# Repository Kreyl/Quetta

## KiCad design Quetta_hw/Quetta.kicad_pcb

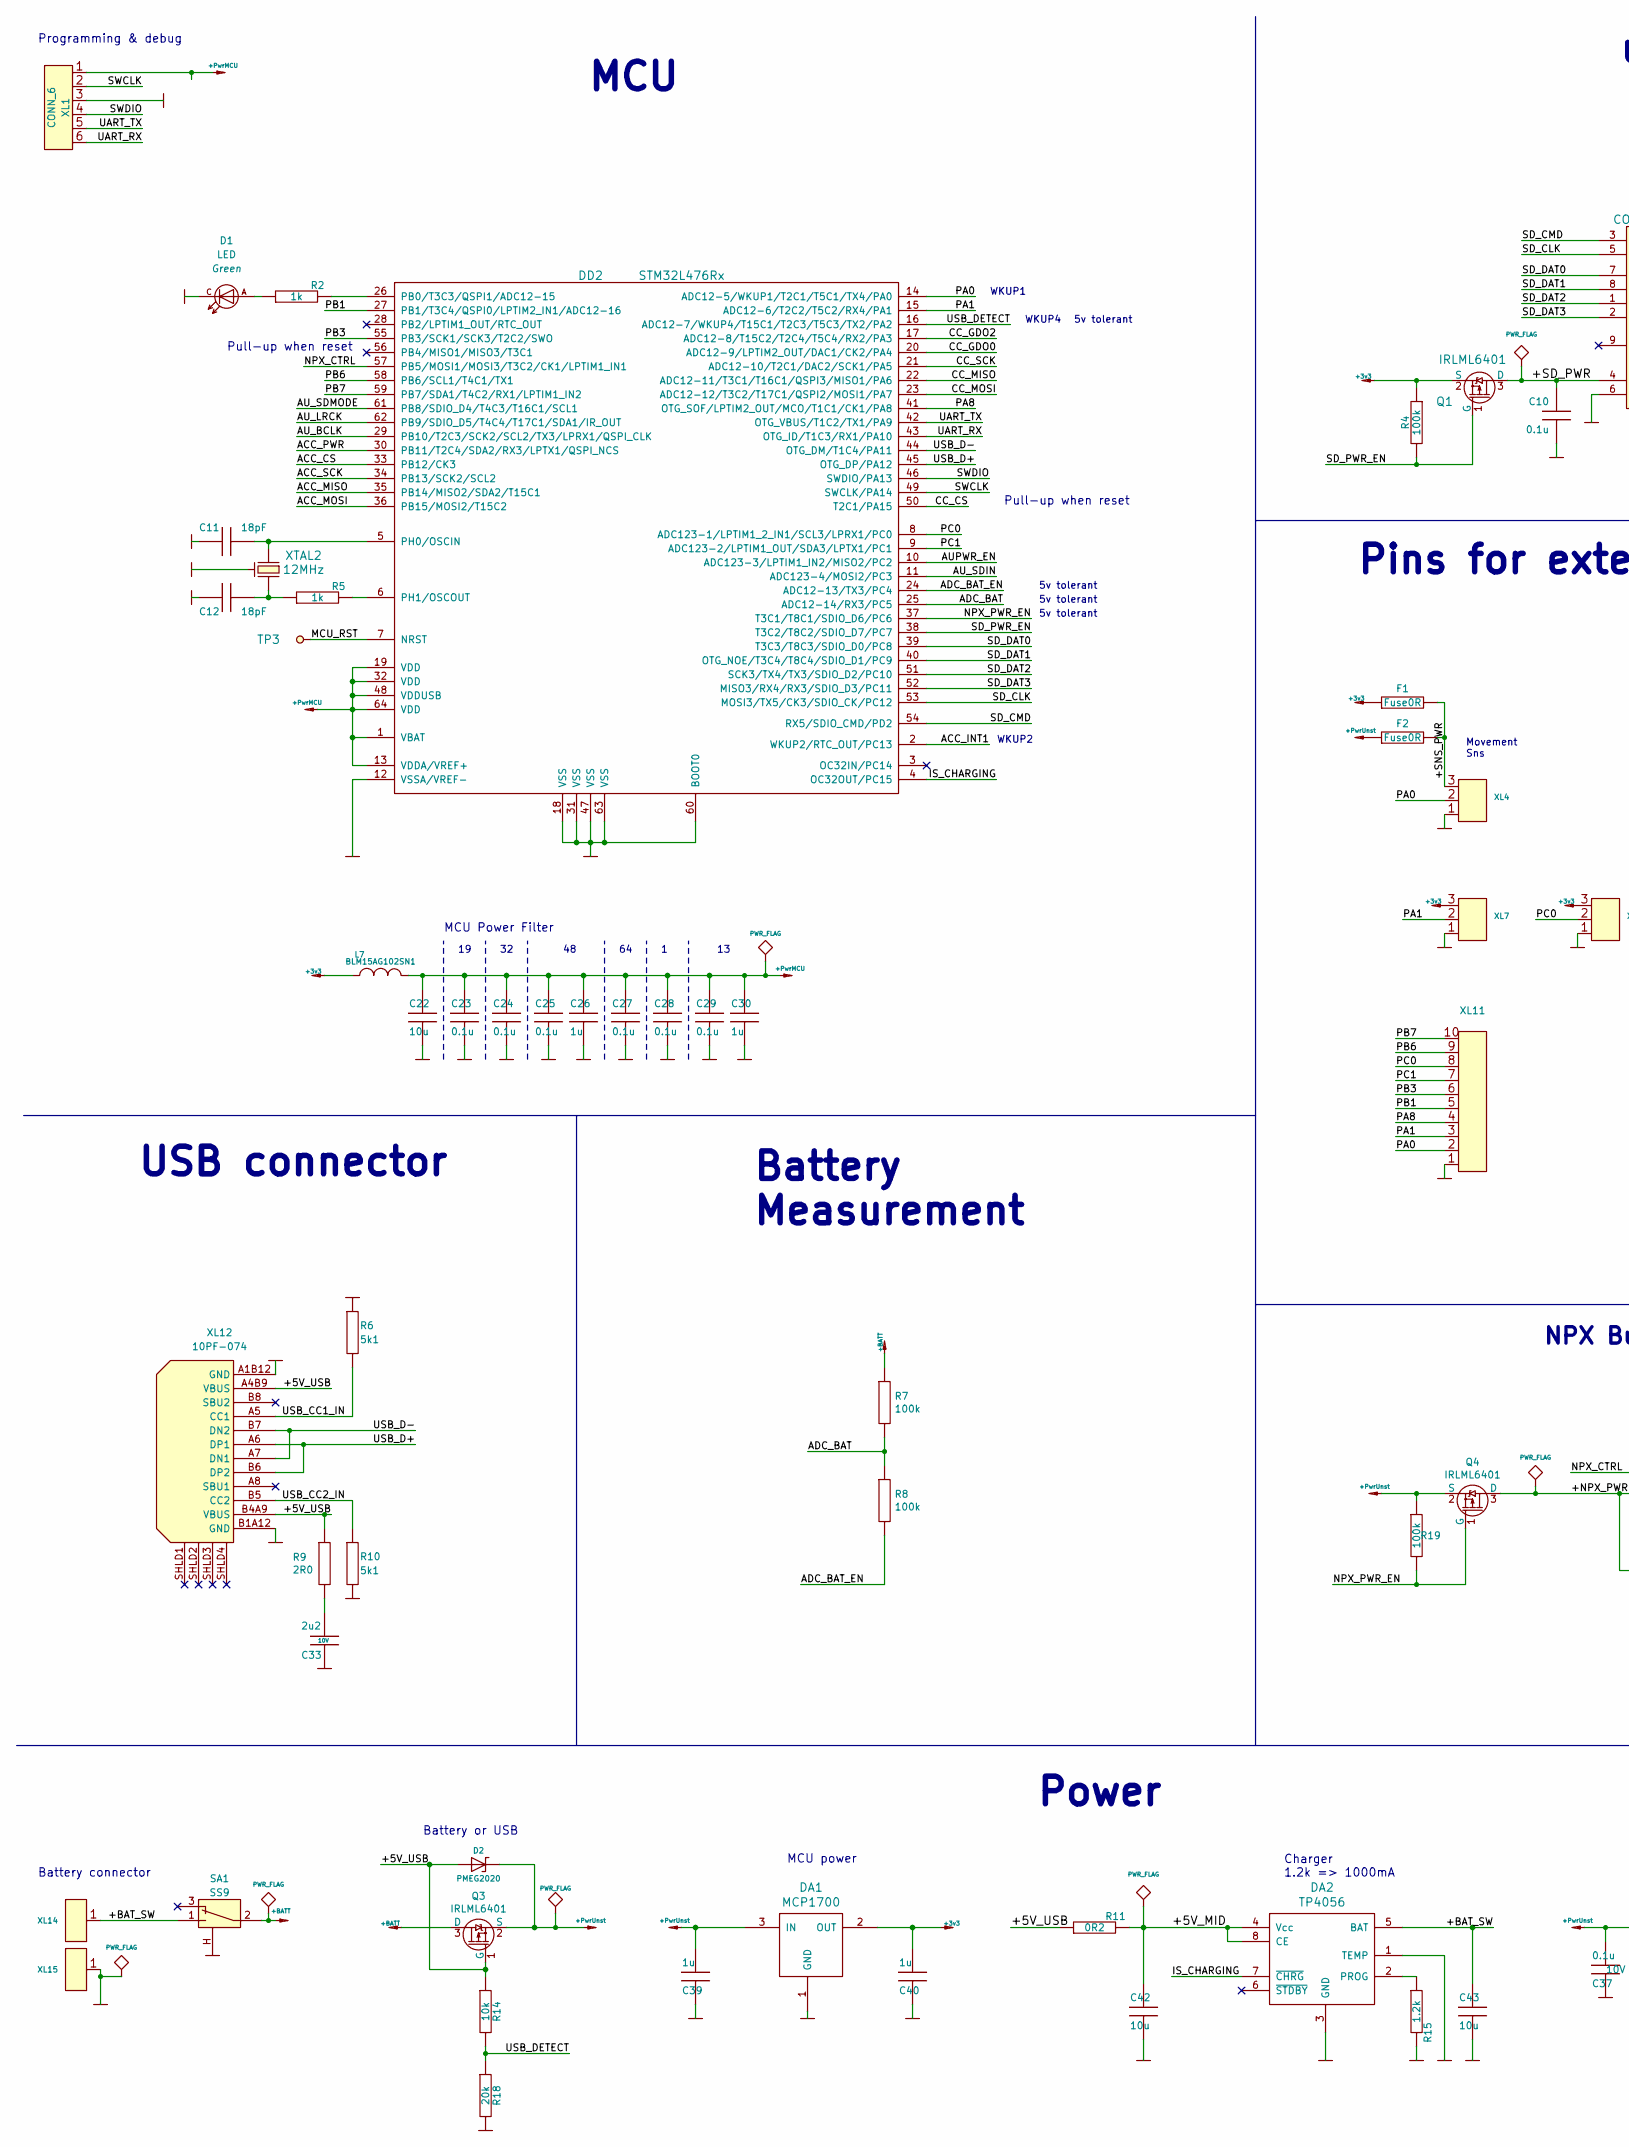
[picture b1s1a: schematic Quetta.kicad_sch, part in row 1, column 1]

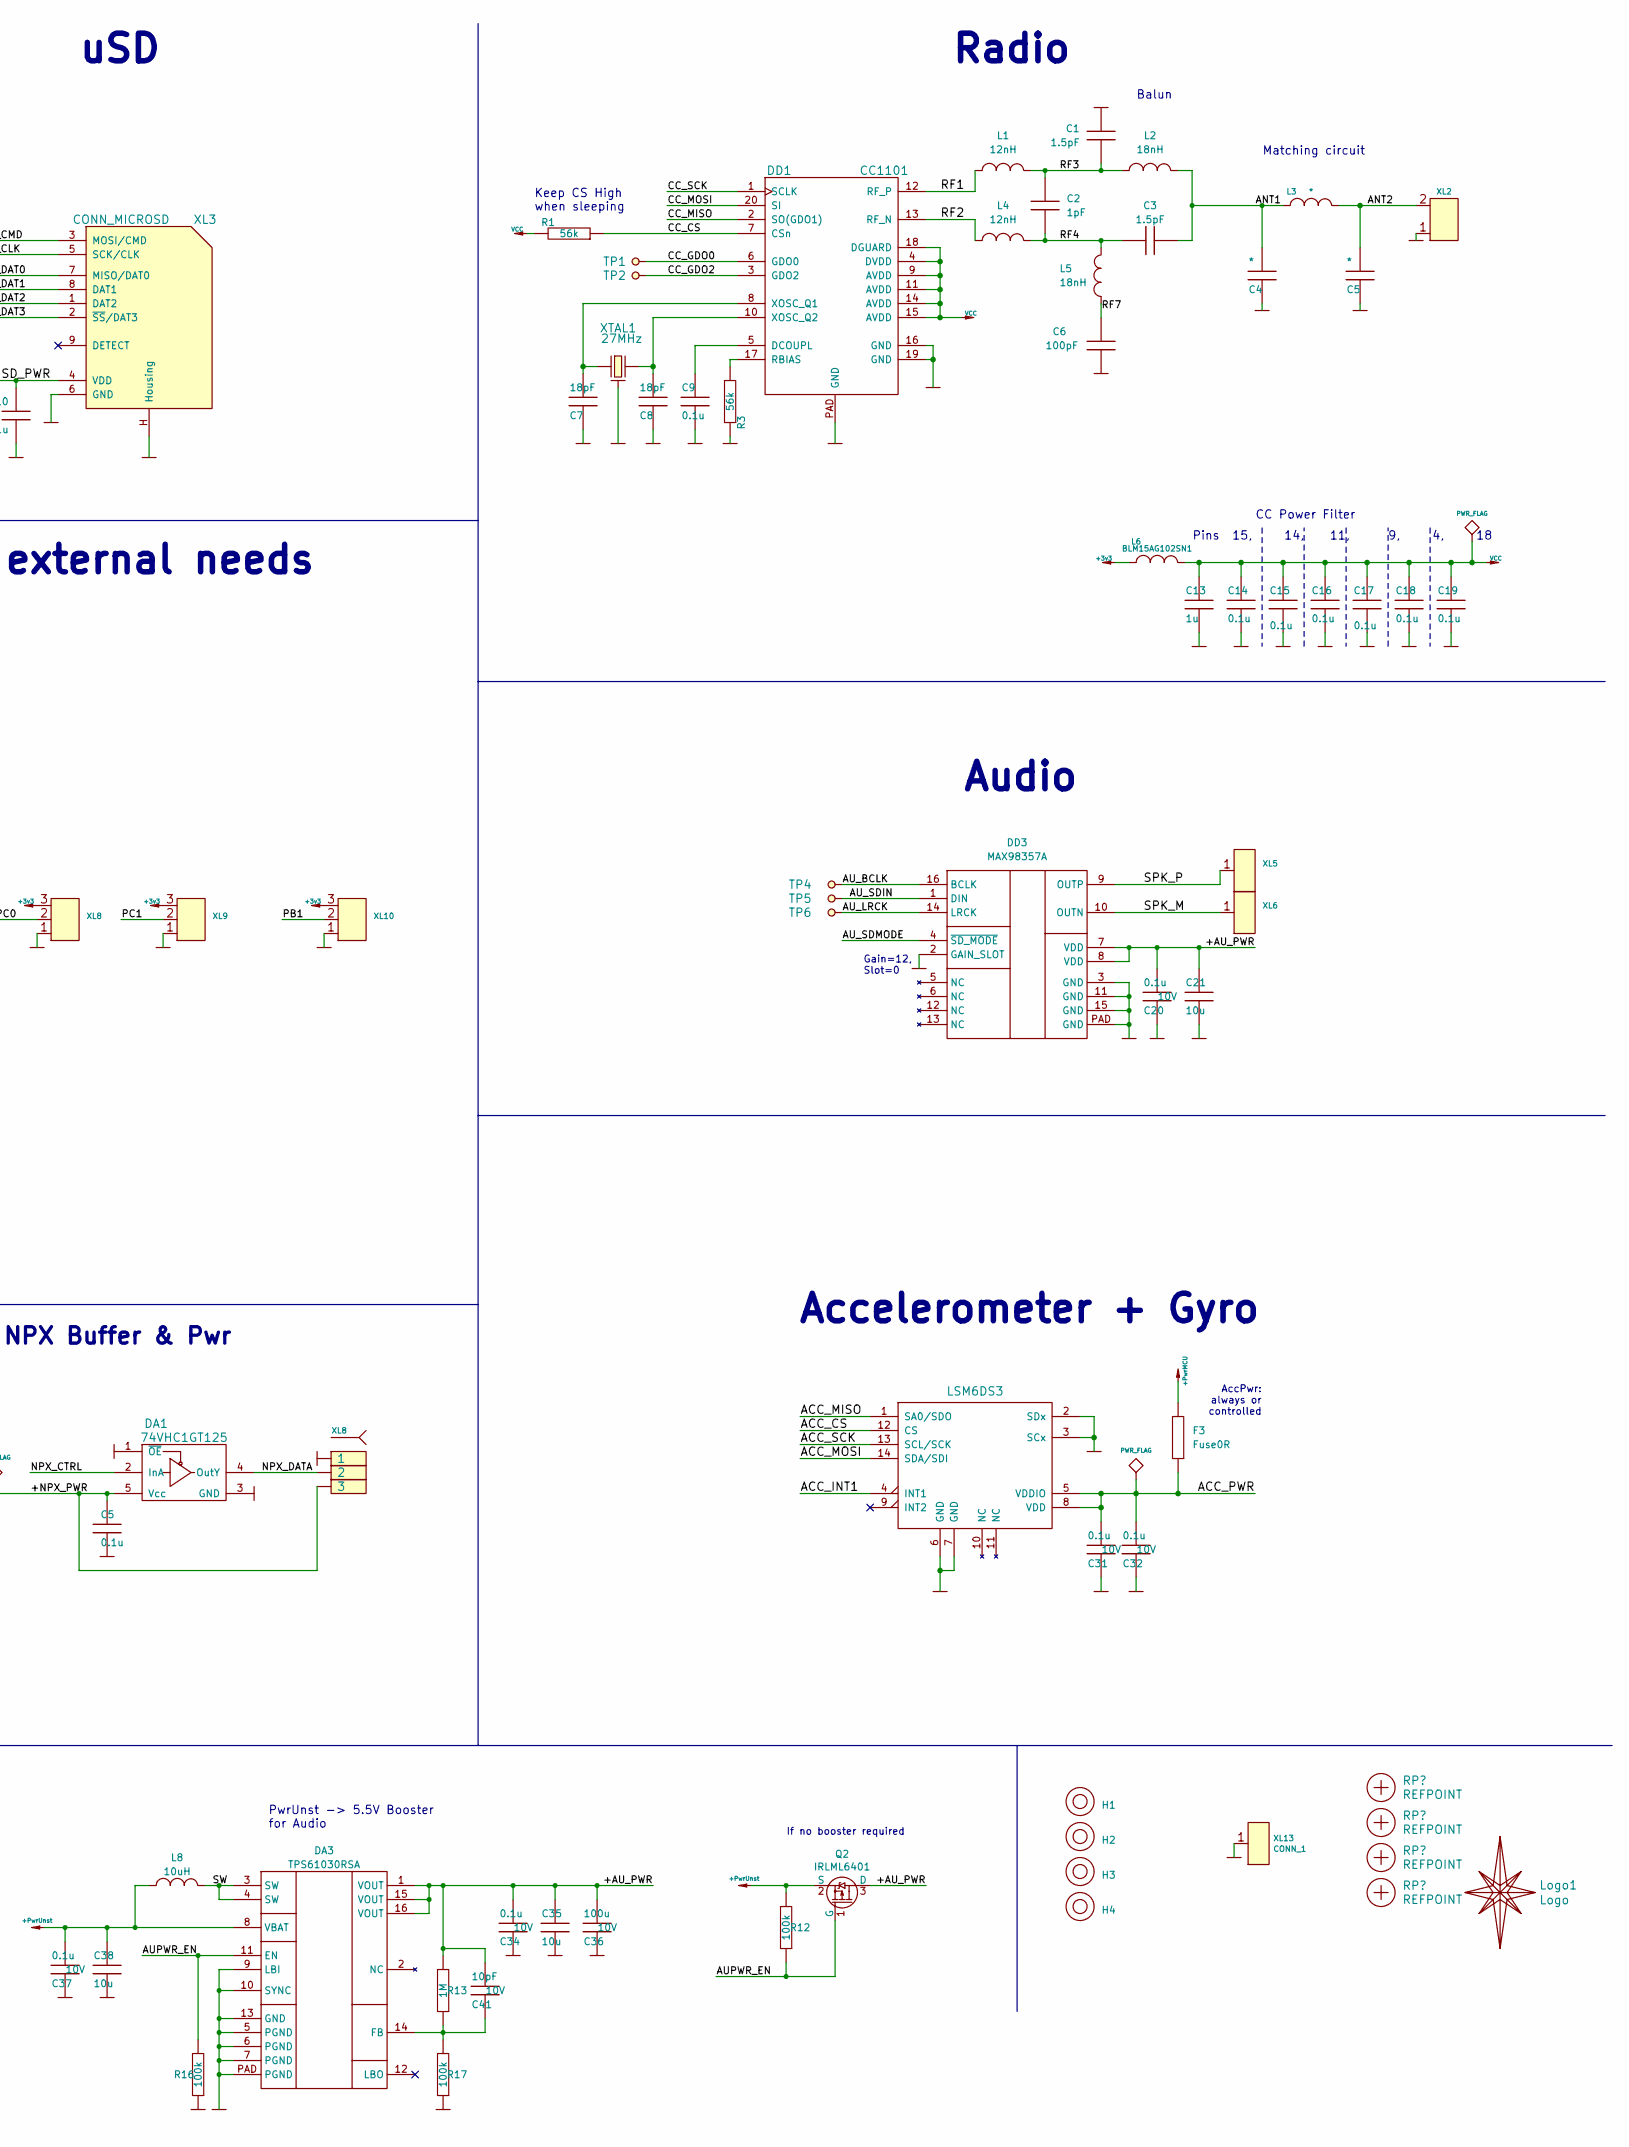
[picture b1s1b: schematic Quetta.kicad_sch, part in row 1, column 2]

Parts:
C1, C3: 1.5pF; CAP_0402; Tolerance 20%; Voltage 10V
C2: 1pF; CAP_0402; Tolerance 20%; Voltage 10V
C4: *; CAP_0402
C5, C20, C31, C32, C34, C37: 0.1u; CAP_0603_Silks; Tolerance 20%; Voltage 10V
C6: 100pF; CAP_0402; Tolerance 20%; Voltage 10V
C7, C8, C11, C12: 18pF; CAP_0603_Silks
C9, C10, C14, C15, C16, C17, C18, C19, C23, C24, C25, C27, C28, C29: 0.1u; CAP_0603_Silks
C13, C26, C30, C39, C40: 1u; CAP_0603_Silks
C21, C22, C35, C38, C42, C43: 10u; CAP_0603_Silks
C33: 2u2; CAP_0603_Silks; Tolerance 20%; Voltage 10V
C36: 100u; CAP_1206; Tolerance 20%; Voltage 10V
C41: 10pF; CAP_0603_Silks; Tolerance 20%; Voltage 10V
D1: LED; LED_0603
D2: PMEG2020; SOD323
DA1: MCP1700; SOT23-3A
DA2: TP4056; SO8_150MIL
DA3: TPS61030RSA; QFN16_0d65_EP2d7
DD1: CC1101; QFN20
DD2: STM32L476Rx; LQFP64
DD3: MAX98357A; QFN-16_EP_3x3_Pitch0.5mm
DD4: LSM6DS3; 14_3x2d5_p0d5
F1, F2, F3: Fuse0R; RES_0603_FUSE
H1, H2, H3, H4: Hole2d2_out4_NoMetal
L1, L4: 12nH; IND_0402; Tolerance 20%
L2, L5: 18nH; IND_0402; Tolerance 20%
L3: *; IND_0402
L6, L7: BLM15AG102SN1; IND_0402
L8: 10uH; SDR0604; Tolerance 20%
Logo1: Logo; Ostranna_8x8
Q1, Q2, Q3, Q4: IRLML6401; SOT23-3
R1, R3: 56k; RES_0603_Silks
R2, R5: 1k; RES_0603_Silks
R4, R7, R8, R12, R16, R17, R19: 100k; RES_0603_Silks
R6, R10: 5k1; RES_0603_Silks; Tolerance 1%
R9: 2R0; RES_0603_Silks; Tolerance 1%
R11: 0R2; RES_1206
R13: 1M; RES_0603_Silks
R14: 10k; RES_0603_Silks; Tolerance 1%
R15: 1.2k; RES_0603_Silks
R18: 20k; RES_0603_Silks; Tolerance 1%
RP1, RP2, RP3, RP4: REFPOINT; REF_POINT_1MM
SA1: SS9; SW_SS9
TP1, TP2, TP3, TP4, TP5, TP6: TESTPOINT; TESTPOINT_1MM
XL1: CONN_6; PLS-6
XL2: CONN_2; PLS-2
XL3: CONN_MICROSD; MICROSD_EJECTOR_TFWF1
XL4, XL7, XL9, XL10: CONN_3; PLS-3
XL5, XL6, XL13: CONN_1; PLS-1Rnd
XL8: SOCKET_3; PLS-3
XL11: CONN_10; PLS-10
XL12: 10PF-074; USBC_10PF-074
XL14: CONN_1; Round_1MM5
XL15: CONN_1; Square_1MM5
XTAL1: 27MHz; 03225C4
XTAL2: 12MHz; 03225C4

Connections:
+BATT: Q3.3 (D), R7.1, SA1.2
+PwrMCU: C22.2, C23.2, C24.2, C25.2, C26.2, C27.2, C28.2, C29.2, C30.2, DD2.1 (VBAT), DD2.13 (VDDA/VREF+), DD2.19 (VDD), DD2.32 (VDD), DD2.48 (VDDUSB), DD2.64 (VDD), F3.1, L7.1, XL1.1
/+5V_MID: C42.2, DA2.4 (Vcc), DA2.8 (CE), R11.2
/+5V_USB: D2.A, Q3.1 (G), R9.1, R11.1, R14.1, XL12.A4B9 (VBUS), XL12.B4A9 (VBUS)
/+AU_PWR: C20.1, C21.2, C34.1, C35.2, C36.1, C41.1, DA3.1 (VOUT), DA3.15 (VOUT), DA3.16 (VOUT), DD3.7 (VDD), DD3.8 (VDD), Q2.3 (D), R13.1
/+BAT_SW: C43.2, DA2.5 (BAT), SA1.1, XL14.1
/+SD_PWR: C10.1, Q1.3 (D), XL3.4 (VDD)
/+SNS_PWR: F1.2, F2.2, XL4.3
/ACC_CS: DD2.33 (PB12/CK3), DD4.12 (CS)
/ACC_INT1: DD2.2 (WKUP2/RTC_OUT/PC13), DD4.4 (INT1)
/ACC_MISO: DD2.35 (PB14/MISO2/SDA2/T15C1), DD4.1 (SA0/SDO)
/ACC_MOSI: DD2.36 (PB15/MOSI2/T15C2), DD4.14 (SDA/SDI)
/ACC_PWR: C31.1, C32.1, DD2.30 (PB11/T2C4/SDA2/RX3/LPTX1/QSPI_NCS), DD4.5 (VDDIO), DD4.8 (VDD), F3.2
/ACC_SCK: DD2.34 (PB13/SCK2/SCL2), DD4.13 (SCL/SCK)
/ADC_BAT: DD2.25 (ADC12-14/RX3/PC5), R7.2, R8.1
/ADC_BAT_EN: DD2.24 (ADC12-13/TX3/PC4), R8.2
/ANT1: C3.2, C4.1, L2.1, L3.2
/AUPWR_EN: DA3.11 (EN), DD2.10 (ADC123-3/LPTIM1_IN2/MISO2/PC2), Q2.1 (G), R12.2, R16.1
/AU_BCLK: DD2.29 (PB10/T2C3/SCK2/SCL2/TX3/LPRX1/QSPI_CLK), DD3.16 (BCLK), TP4.1
/AU_LRCK: DD2.62 (PB9/SDIO_D5/T4C4/T17C1/SDA1/IR_OUT), DD3.14 (LRCK), TP6.1
/AU_SDIN: DD2.11 (ADC123-4/MOSI2/PC3), DD3.1 (DIN), TP5.1
/AU_SDMODE: DD2.61 (PB8/SDIO_D4/T4C3/T16C1/SCL1), DD3.4 (~SD_MODE)
/CC_CS: DD1.7 (CSn), DD2.50 (T2C1/PA15), R1.1
/CC_GDO0: DD1.6 (GDO0), DD2.20 (ADC12-9/LPTIM2_OUT/DAC1/CK2/PA4), TP1.1
/CC_GDO2: DD1.3 (GDO2), DD2.17 (ADC12-8/T15C2/T2C4/T5C4/RX2/PA3), TP2.1
/CC_MISO: DD1.2 (SO(GDO1)), DD2.22 (ADC12-11/T3C1/T16C1/QSPI3/MISO1/PA6)
/CC_MOSI: DD1.20 (SI), DD2.23 (ADC12-12/T3C2/T17C1/QSPI2/MOSI1/PA7)
/CC_SCK: DD1.1 (SCLK), DD2.21 (ADC12-10/T2C1/DAC2/SCK1/PA5)
/IS_CHARGING: DA2.7 (~CHRG), DD2.4 (OC32OUT/PC15)
/MCU_RST: DD2.7 (NRST), TP3.1
/NPX_PWR_EN: DD2.37 (T3C1/T8C1/SDIO_D6/PC6), Q4.1 (G), R19.2
/PA0: DD2.14 (ADC12-5/WKUP1/T2C1/T5C1/TX4/PA0), XL4.2 (PM), XL11.2
/PA1: DD2.15 (ADC12-6/T2C2/T5C2/RX4/PA1), XL7.2 (PM), XL11.3
/PA8: DD2.41 (OTG_SOF/LPTIM2_OUT/MCO/T1C1/CK1/PA8), XL11.4
/PB1: DD2.27 (PB1/T3C4/QSPI0/LPTIM2_IN1/ADC12-16), XL10.2 (PM), XL11.5
/PB3: DD2.55 (PB3/SCK1/SCK3/T2C2/SWO), XL11.6
/PB6: DD2.58 (PB6/SCL1/T4C1/TX1), XL11.9
/PB7: DD2.59 (PB7/SDA1/T4C2/RX1/LPTIM1_IN2), XL11.10
/PC1: DD2.9 (ADC123-2/LPTIM1_OUT/SDA3/LPTX1/PC1), XL9.2 (PM), XL11.7
/RF1: DD1.12 (RF_P), L1.2
/RF2: DD1.13 (RF_N), L4.2
/RF3: C1.1, C2.1, L1.1, L2.2
/RF4: C2.2, C3.1, L4.1, L5.1
/RF7: C6.2, L5.2
/SD_CLK: DD2.53 (MOSI3/TX5/CK3/SDIO_CK/PC12), XL3.5 (SCK/CLK)
/SD_CMD: DD2.54 (RX5/SDIO_CMD/PD2), XL3.3 (MOSI/CMD)
/SD_DAT0: DD2.39 (T3C3/T8C3/SDIO_D0/PC8), XL3.7 (MISO/DAT0)
/SD_DAT1: DD2.40 (OTG_NOE/T3C4/T8C4/SDIO_D1/PC9), XL3.8 (DAT1)
/SD_DAT2: DD2.51 (SCK3/TX4/TX3/SDIO_D2/PC10), XL3.1 (DAT2)
/SD_DAT3: DD2.52 (MISO3/RX4/RX3/SDIO_D3/PC11), XL3.2 (~SS/DAT3)
/SD_PWR_EN: DD2.38 (T3C2/T8C2/SDIO_D7/PC7), Q1.1 (G), R4.2
/SPK_M: DD3.10 (OUTN), XL6.1
/SPK_P: DD3.9 (OUTP), XL5.1
/SW: DA3.3 (SW), DA3.4 (SW), L8.1
/SWCLK: DD2.49 (SWCLK/PA14), XL1.2
/SWDIO: DD2.46 (SWDIO/PA13), XL1.4
/UART_RX: DD2.43 (OTG_ID/T1C3/RX1/PA10), XL1.6
/UART_TX: DD2.42 (OTG_VBUS/T1C2/TX1/PA9), XL1.5
/USB_CC1_IN: R6.2, XL12.A5 (CC1)
/USB_CC2_IN: R10.1, XL12.B5 (CC2)
/USB_D+: DD2.45 (OTG_DP/PA12), XL12.A6 (DP1), XL12.B6 (DP2)
/USB_D-: DD2.44 (OTG_DM/T1C4/PA11), XL12.A7 (DN1), XL12.B7 (DN2)
/USB_DETECT: DD2.16 (ADC12-7/WKUP4/T15C1/T2C3/T5C3/TX2/PA2), R14.2, R18.1
unnamed: C12.1, R5.1, XTAL2.2
unnamed: C33.1, R9.2
unnamed: D1.A, R2.1
unnamed: DA2.2 (PROG), R15.1
unnamed: C41.2, DA3.14 (FB), R13.2, R17.1
unnamed: C9.2, DD1.5 (DCOUPL)
unnamed: DD1.17 (RBIAS), R3.1
unnamed: C7.1, DD1.8 (XOSC_Q1), XTAL1.1
unnamed: C8.1, DD1.10 (XOSC_Q2), XTAL1.2
unnamed: DD2.26 (PB0/T3C3/QSPI1/ADC12-15), R2.2
unnamed: C11.1, DD2.5 (PH0/OSCIN), XTAL2.1
unnamed: DD2.6 (PH1/OSCOUT), R5.2
VCC: C13.1, C14.1, C15.1, C16.1, C17.1, C18.1, C19.1, DD1.4 (DVDD), DD1.9 (AVDD), DD1.11 (AVDD), DD1.14 (AVDD), DD1.15 (AVDD), DD1.18 (DGUARD), L6.1, R1.2

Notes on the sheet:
Pins 15, 14, 11, 9, 4, 18
WKUP1
USB connector
Battery Measurement
MCU power
WKUP2
Movement Sns
CC Power Filter
AccPwr: always or controlled
Charger 1.2k => 1000mA
Power
Keep CS High when sleeping
WKUP4
5v tolerant
PwrUnst -> 5.5V Booster for Audio
Programming & debug
NPX Buffer & Pwr
Battery connector
Accelerometer + Gyro
Pins for external needs
Audio
Pull-up when reset
If no booster required
Gain=12, Slot=0
Matching circuit
MCU Power Filter
Balun
uSD
Radio
Battery or USB
MCU

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
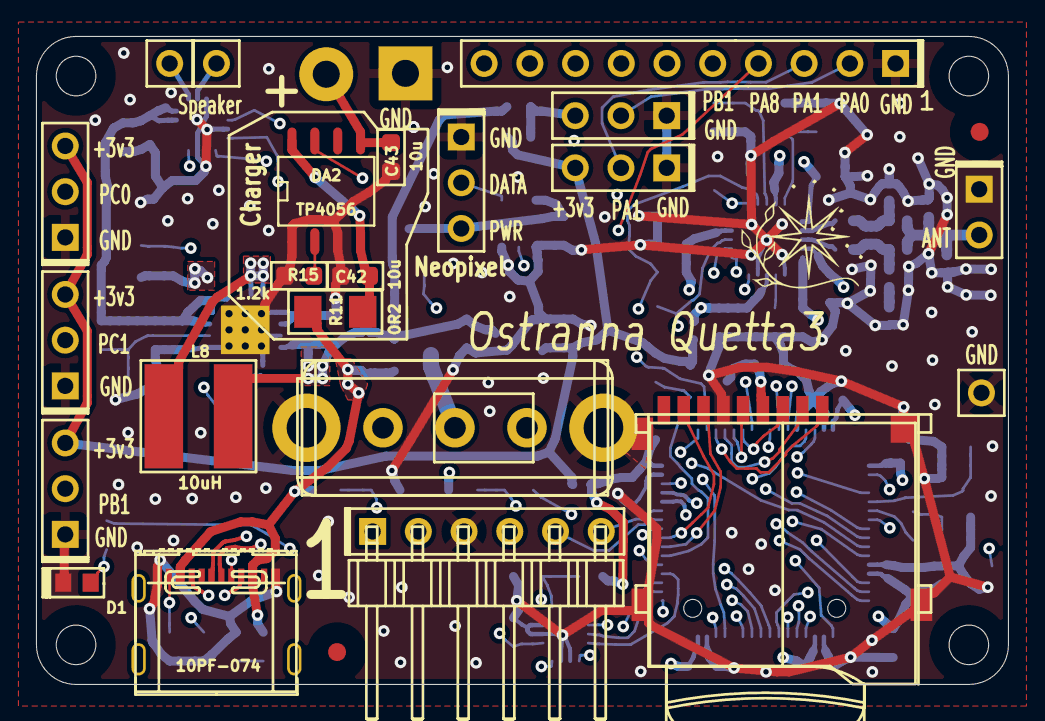
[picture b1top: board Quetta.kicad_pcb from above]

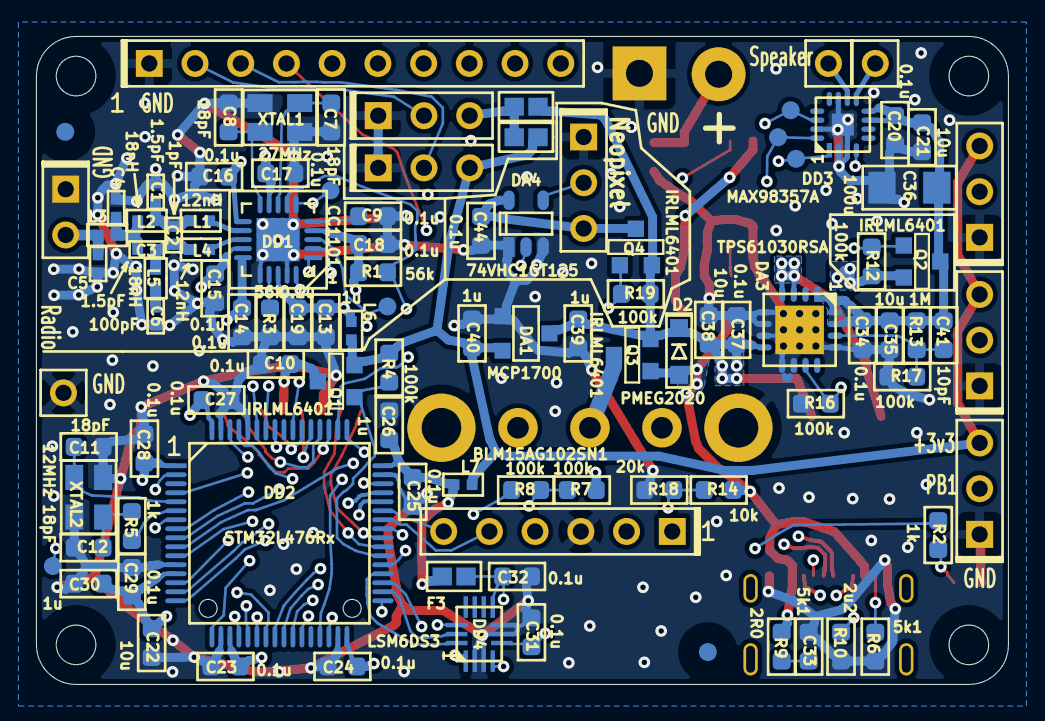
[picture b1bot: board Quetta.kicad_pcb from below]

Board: 4 copper layers, 54.0 x 36.0 mm, 122 parts (91 on the bottom side), 84 nets.

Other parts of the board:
C44: 0.1u; CAP_0603_Silks
DA4: 74VHC1GT125; SOT23-5
XL16: SOCKET_3; PLS-3

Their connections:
/NPX_DATA: DA4.4 (OutY), XL16.2

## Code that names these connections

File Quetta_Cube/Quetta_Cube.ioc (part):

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Mcu.Name=STM32L476R(C-E-G)Tx
Mcu.Package=LQFP64
Mcu.UserName=STM32L476RCTx
PA0.Mode=SYS_WakeUp0
PA0.Signal=SYS_WKUP1
PA10.Mode=Asynchronous
PA10.Signal=USART1_RX
PA11.Mode=Device_Only
PA11.Signal=USB_OTG_FS_DM
PA12.Mode=Device_Only
PA12.Signal=USB_OTG_FS_DP
PA13\ (JTMS-SWDIO).Mode=Serial_Wire
PA13\ (JTMS-SWDIO).Signal=SYS_JTMS-SWDIO
PA14\ (JTCK-SWCLK).Mode=Serial_Wire
PA14\ (JTCK-SWCLK).Signal=SYS_JTCK-SWCLK
PA2.Mode=SYS_WakeUp3
PA2.Signal=SYS_WKUP4
PA5.Mode=Full_Duplex_Master
PA5.Signal=SPI1_SCK
PA6.Mode=Full_Duplex_Master
PA6.Signal=SPI1_MISO
PA7.Mode=Full_Duplex_Master
PA7.Signal=SPI1_MOSI
PA9.Mode=Asynchronous
PA9.Signal=USART1_TX
PB0.Signal=S_TIM3_CH3
PB10.Mode=SAI_A_Master
PB10.Signal=SAI1_SCK_A
PB12.Signal=GPIO_Output
PB13.Mode=Full_Duplex_Master
PB13.Signal=SPI2_SCK
PB14.Mode=Full_Duplex_Master
PB14.Signal=SPI2_MISO
PB15.Mode=Full_Duplex_Master
PB15.Signal=SPI2_MOSI
PB3\ (JTDO-TRACESWO).Mode=TX_Only_Simplex_Unidirect_Master
PB3\ (JTDO-TRACESWO).Signal=SPI3_SCK
PB5.Mode=TX_Only_Simplex_Unidirect_Master
PB5.Signal=SPI3_MOSI
PB9.Mode=SAI_A_Master
PB9.Signal=SAI1_FS_A
PC10.Mode=SD_4_bits_Wide_bus
PC10.Signal=SDMMC1_D2
PC11.Mode=SD_4_bits_Wide_bus
PC11.Signal=SDMMC1_D3
PC12.Mode=SD_4_bits_Wide_bus
PC12.Signal=SDMMC1_CK
PC13.Mode=SYS_WakeUp1
PC13.Signal=SYS_WKUP2
PC3.Mode=SAI_A_Master
PC3.Signal=SAI1_SD_A
PC8.Mode=SD_4_bits_Wide_bus
PC8.Signal=SDMMC1_D0
PC9.Mode=SD_4_bits_Wide_bus
PC9.Signal=SDMMC1_D1
PD2.Mode=SD_4_bits_Wide_bus
PD2.Signal=SDMMC1_CMD
PH0-OSC_IN\ (PH0).Mode=HSE-External-Oscillator
PH0-OSC_IN\ (PH0).Signal=RCC_OSC_IN
PH1-OSC_OUT\ (PH1).Mode=HSE-External-Oscillator
PH1-OSC_OUT\ (PH1).Signal=RCC_OSC_OUT
RCC.HSE_VALUE=8000000
board=custom

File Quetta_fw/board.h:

/*
 * board.h
 *
 *  Created on: 10 01 2024
 *      Author: Kreyl
 */

#ifndef BOARD_H__
#define BOARD_H__

// ==== General ====
#define APP_NAME            "QuettaPortrait"

// MCU type as defined in the ST header.
#define STM32L476xx

// Freq of external crystal if any. Leave it here even if not used.
#define CRYSTAL_FREQ_HZ         12000000

//  Periphery
#define I2C1_ENABLED            FALSE
#define I2C2_ENABLED            FALSE
#define I2C3_ENABLED            FALSE

#define ADC_REQUIRED            FALSE
#define SIMPLESENSORS_ENABLED   TRUE
#define STM32_DMA_REQUIRED      TRUE    // Leave this macro name for OS

#if 1 // ========================= Timers ======================================
// OS timer settings
#define STM32_ST_IRQ_PRIORITY   2
#define STM32_ST_USE_TIMER      5
#define SYS_TIM_CLK             (Clk.APB1FreqHz)    // Timer 5 is clocked by APB1

#endif

#if 1 // ========================== GPIO =======================================
// EXTI
#define INDIVIDUAL_EXTI_IRQ_REQUIRED    FALSE

// Debug pin
#define DBG_PIN         GPIOA, 8
#define DBG_HI()        PinSetHi(DBG_PIN)
#define DBG_LO()        PinSetLo(DBG_PIN)
#define DBG_TOGGLE()    PinToggle(DBG_PIN)

// WKUP pin
#define SNS_INPUT       GPIOA, 0 // WKUP1
// Charging
#define IS_CHARGING_PIN GPIOC, 15
// USB detect
#define USB_DETECT_PIN  GPIOA, 2 // WKUP4

// LEDs
#define LED_PIN         { GPIOB, 0, TIM3, 3, invNotInverted, omPushPull, 255 }

// Audio
#define AU_SAI          SAI1
#define AU_SAI_A        SAI1_Block_A
#define AU_SAI_RccEn()  RCC->APB2ENR |= RCC_APB2ENR_SAI1EN
#define AU_SAI_RccDis() RCC->APB2ENR &= ~RCC_APB2ENR_SAI1EN
#define AU_SDMODE       GPIOB, 8, omPushPull
#define AU_PWREN        GPIOC, 2, omPushPull
#define AU_LRCK         GPIOB, 9, omPushPull, pudNone, AF13
#define AU_SCLK         GPIOB, 10, omPushPull, pudNone, AF13
#define AU_SDIN         GPIOC, 3, omPushPull, pudNone, AF13 // MOSI; SAI1_A

// Acc
#define ACG_SPI         SPI2
#define ACG_PWR_PIN     GPIOB, 11
#define ACG_CS_PIN      GPIOB, 12
#define ACG_SCK_PIN     GPIOB, 13, omPushPull, pudNone, AF5
#define ACG_MISO_PIN    GPIOB, 14, omPushPull, pudNone, AF5
#define ACG_MOSI_PIN    GPIOB, 15, omPushPull, pudNone, AF5
#define ACG_IRQ_PIN     GPIOC, 13 // WKUP2

// ADC
#define ADC_BAT_EN      GPIOC, 4, omOpenDrain
#define ADC_BAT         GPIOC, 5

// SD
#define SD_PWR_PIN      GPIOC, 7
#define SD_AF           AF12
#define SD_DAT0         GPIOC,  8, omPushPull, pudPullUp, SD_AF
#define SD_DAT1         GPIOC,  9, omPushPull, pudPullUp, SD_AF
#define SD_DAT2         GPIOC, 10, omPushPull, pudPullUp, SD_AF
#define SD_DAT3         GPIOC, 11, omPushPull, pudPullUp, SD_AF
#define SD_CLK          GPIOC, 12, omPushPull, pudNone,   SD_AF
#define SD_CMD          GPIOD,  2, omPushPull, pudPullUp, SD_AF

// CMD UART
#define CMD_UART_GPIO   GPIOA
#define CMD_UART_TX_PIN 9
#define CMD_UART_RX_PIN 10

// USB
#define USB_DM          GPIOA, 11
#define USB_DP          GPIOA, 12
#define USB_AF          AF10

// Radio: SPI, PGpio, Sck, Miso, Mosi, Cs, Gdo0
#define CC_Setup0       SPI1, GPIOA, 5,6,7, GPIOA,15, GPIOA,4

// I2C
#define I2CA            i2c3
#define I2C3_GPIO       GPIOC
#define I2C3_SCL        0
#define I2C3_SDA        1
#define I2C_AF          AF4
// i2cclkPCLK1, i2cclkSYSCLK, i2cclkHSI
#define I2C_CLK_SRC     i2cclkHSI
#define I2C_BAUDRATE_HZ 400000
// I2C PullUp
#define I2C_PULLUP      GPIOC, 2, omPushPull

#endif // GPIO


#if 1 // =========================== DMA =======================================
#define ADC_DMA         STM32_DMA_STREAM_ID(1, 1)
#define CRC_DMA         STM32_DMA_STREAM_ID(1, 2)
#define ACG_DMA_RX      STM32_DMA_STREAM_ID(1, 4)
#define ACG_DMA_TX      STM32_DMA_STREAM_ID(1, 5)
#define SAI_DMA_A       STM32_DMA_STREAM_ID(2, 1)
#define STM32_SDC_SDMMC1_DMA_STREAM   STM32_DMA_STREAM_ID(2, 5)
#define UART_DMA_TX     STM32_DMA_STREAM_ID(2, 6)
#define UART_DMA_RX     STM32_DMA_STREAM_ID(2, 7)

// ==== Uart ====
// Remap is made automatically if required
#define UART_DMA_CHNL   2
#define UART_DMA_TX_MODE(Chnl) (STM32_DMA_CR_CHSEL(Chnl) | DMA_PRIORITY_LOW | STM32_DMA_CR_MSIZE_BYTE | STM32_DMA_CR_PSIZE_BYTE | STM32_DMA_CR_MINC | STM32_DMA_CR_DIR_M2P | STM32_DMA_CR_TCIE)
#define UART_DMA_RX_MODE(Chnl) (STM32_DMA_CR_CHSEL(Chnl) | DMA_PRIORITY_MEDIUM | STM32_DMA_CR_MSIZE_BYTE | STM32_DMA_CR_PSIZE_BYTE | STM32_DMA_CR_MINC | STM32_DMA_CR_DIR_P2M | STM32_DMA_CR_CIRC)

// ==== ACG ====
#define ACG_DMA_CHNL    1

// ==== SAI ====
#define SAI_DMA_CHNL    1

// ==== I2C ====
#define I2C_USE_DMA         FALSE
#if I2C1_ENABLED
#define I2C1_DMA_TX     STM32_DMA_STREAM_ID(1, 6)
#define I2C1_DMA_RX     STM32_DMA_STREAM_ID(1, 7)
#define I2C1_DMA_CHNL   3
#endif
#if I2C2_ENABLED
#define I2C2_DMA_TX     STM32_DMA_STREAM_ID(1, 4)
#define I2C2_DMA_RX     STM32_DMA_STREAM_ID(1, 5)
#define I2C2_DMA_CHNL   3
#endif
#if I2C3_ENABLED
#define I2C3_DMA_TX     STM32_DMA_STREAM_ID(1, 2)
#define I2C3_DMA_RX     STM32_DMA_STREAM_ID(1, 3)
#define I2C3_DMA_CHNL   3
#endif

#define ADC_DMA_MODE    STM32_DMA_CR_CHSEL(0) |   /* DMA1 Stream1 Channel0 */ \
                        DMA_PRIORITY_LOW | \
                        STM32_DMA_CR_MSIZE_HWORD | \
                        STM32_DMA_CR_PSIZE_HWORD | \
                        STM32_DMA_CR_MINC |       /* Memory pointer increase */ \
                        STM32_DMA_CR_DIR_P2M |    /* Direction is peripheral to memory */ \
                        STM32_DMA_CR_TCIE         /* Enable Transmission Complete IRQ */

#endif // DMA

#if 1 // ========================== USART ======================================
#define PRINTF_FLOAT_EN FALSE
#define UART_TXBUF_SZ   2048
#define UART_RXBUF_SZ   1024
#define CMD_BUF_SZ      1024

#define CMD_UART        USART1

#define CMD_UART_PARAMS \
    CMD_UART, CMD_UART_GPIO, CMD_UART_TX_PIN, CMD_UART_GPIO, CMD_UART_RX_PIN, \
    UART_DMA_TX, UART_DMA_RX, UART_DMA_TX_MODE(UART_DMA_CHNL), UART_DMA_RX_MODE(UART_DMA_CHNL), \
    uartclkHSI // Use independent clock

#endif

#endif //BOARD_H__

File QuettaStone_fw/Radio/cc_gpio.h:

/*
 * cc_gpio.h
 *
 *  Created on: Nov 28, 2013
 *      Author: kreyl
 */

#pragma once

// Pins
#define CC_GPIO     GPIOA
//#define CC_GDO2     2
#define CC_GDO0     4
#define CC_SCK      5
#define CC_MISO     6
#define CC_MOSI     7
#define CC_CS       10

#if defined STM32L1XX || defined STM32F2XX
#if CC_GDO0 == 0
#define GDO0_IRQ_HANDLER     Vector58
#elif CC_GDO0 == 1
#define GDO0_IRQ_HANDLER     Vector5C
#elif CC_GDO0 == 2
#define GDO0_IRQ_HANDLER     Vector60
#elif CC_GDO0 == 3
#define GDO0_IRQ_HANDLER     Vector64
#elif CC_GDO0 == 4
#define GDO0_IRQ_HANDLER     Vector68
#endif

// SPI
#define CC_SPI      SPI1
#if defined STM32L1XX || defined STM32F2XX
#define CC_SPI_AF   AF5
#elif defined STM32F030
#define CC_SPI_AF   AF0
#endif
#endif // L15xx

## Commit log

2015-06-14 + HW + Portrait + Stone
2015-06-14 * Switch to kl_lib
2015-06-15 + i2c BusScan + Acc works
2015-06-15 * i2c timings adjusted
2015-06-15 + Kick time added and printed
2015-06-15 + First sequence detected
2015-06-16 + sequences * Better comparision
2015-06-18 + Hyperspheric comparision + Normalization
2015-06-18 + Normalization ok + Switch to Acc Irq * Sequenced adopted
2015-06-18 * No Acc IRQ. Acc Thread returned. No internal ACC kick detection used, MCU checks accelerations every 20ms and decides if kick occured. * Argentum seq updated to decrease amount of false detection s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
2015-06-18 + Sequences.docx
2016-03-27 + Quetta HW2
2016-03-29 Components choosen
2016-04-13 new pcb
2016-04-14 Components spreaded all over
2016-04-16 TopoR start
2016-04-16 TopoR1
2016-04-16 TopoR +3.3V
2016-04-16 TopoR VCC
2016-04-16 TopoR PWR_VS
2016-04-16 TopoR power complete
2016-04-16 TopoR CC done
2016-04-16 TopoR STM left done
2016-04-16 TopoR STM top done
2016-04-16 TopoR STM bottom done
2016-04-16 TopoR STM right done
2016-04-16 TopoR VS1011 done
2016-04-16 TopoR shld
2016-04-16 TopoR everything but GND
2016-04-16 TopoR GND in process
2016-04-18 TopoR GND
2016-04-18 TopoR GND done
2016-04-18 TopoR checked
2016-04-18 TopoR MORE GND
2016-04-18 TopoR DRC done
2016-04-18 Gerber done
2016-04-19 + Ostranna logo * Vias now all 0.3 drill + Gerbers sent to production
2016-05-20 Proceeding with old libs
2016-05-20 + Soundlist works
2016-05-20 + Accelerometer works
2016-05-20 + CC works
2016-06-10 ignore csv
2017-04-08 * Switch to new OS
2017-04-09 sd not working
2017-04-09 SD ok
2017-04-09 Proceeding with sound
2017-04-09 She is alive again!
2017-04-09 + Soundlist Still two buffers in Sound
2017-04-09 * Double buf issue fixed (was not playing end of file) + Soundlist works ok
2017-04-10 +ws2812 * switch to 16MHz
2017-04-10 * Other effects
2017-04-12 + buttons work
2017-04-12 strange behavior
2017-04-12 logic seems working
2017-04-13 + Timing read frog config
2017-04-13 + Sounlist saves lastN about every dir
2023-12-16 smth
2023-12-16 Everything removed
2023-12-19 Tracing done
2023-12-19 + Gerbers sent to factory
2024-01-10 + Fw compiles
2024-01-10 + SD init ok
2024-01-10 Working on USB
2024-01-10 SD ini read ok
2024-01-12 Usb works Audio works
2024-02-11 starting
2024-02-11 Playing random file
2024-02-12 Must be working. Still no settings checked.
